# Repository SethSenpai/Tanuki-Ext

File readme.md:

# Tanuki-Ext OLED edition

The Tanuki-Ext is a redesign of the original [Tanuki Keyboard](https://github.com/SethSenpai/Tanuki). There were a few things about the original design that were preventing me from using it while coding and doing CAD. Most of all was the lack of dedicated arrow cluster. 

The Tanuki-Ext fixes these issues and aims to create and even more open and accessible keyboard platform to experiment with by moving its firmware over to [CircuitPython](https://circuitpython.org/) and [KMKfw](http://kmkfw.io/). This allows you to access and modify your code without the need for extra programs, compilers or debuggers making it very approachable.

## Layout
Like the original Tanuki keyboard the design has a split spacebar. Holding down the left spacebar brings you to the lower layer for numbers. Holding down the right spacebar brings you to the top layer for symbols. Never move your fingers from the homerow ever again!

Both the firmware and design files of the Tanuki are distributed under GNU GPLv3 and are able to be used for commercial under [specific conditions](https://choosealicense.com/licenses/gpl-3.0/).

## Assembly

Assembling the device is quite straight forward. Create the casing from the files in the `Case` folder. Grab a hold of A `PCB` or handwire the keyboard using an [Raspberry Pi Pico](https://www.raspberrypi.com/products/raspberry-pi-pico/). Put on the backplate and close the whole thing up with 4 bolts. Check out the individual folders for further instructions. 

## Keycaps
Normally a full 104 key keycap set should have enough keys to cover the keyboard properly. Just to be sure I've made a list of the needed keycaps below.

| Size | Amount |
| ---- | ------ |
| 2u | 2 |
| 1u | 37 |
| 1.25u | 8 |

I find the most comfortable keycap profile to be DSA or XDA keycaps since I don't need to worry about the keycap height being all over the place due to the uncommon layout of the Tanuki-Ext.

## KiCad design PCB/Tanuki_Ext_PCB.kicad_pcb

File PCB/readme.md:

# PCB

The PCB was designed in KiCAD 7.0. It is set up to allow you to modify it more easily. It has a couple of GPIO pins broken out as test pads. It also has footprints for WS2812 type LEDS in case you don't want to integrate an OLED screen.

## Ordering PCB
The files in the _export folder contain both the gerbers, BOM and PNP files. These files are needed for a manufacturer to know how to make your pcb. What parts to place on it, and where to place those parts.

I ordered my prototype batch through JLC pcb and the export files are formatted as such. I decided to include them to make the process of making more PCB's as smooth as possible.

If you decide to have boards made at a different manufacturer you should check their knowledge base to make sure the files you give them adhere to their guidelines.

I would not recommend soldering this PCB by hand unless you know what you're doing. Some of the parts cannot be soldered with a soldering iron and require a hot air gun.
## Library
The folder contains a library for KiCAD 7.0 that holds the footprint for the 0.9 inch OLED module that this keyboard integrates. 
## Installing the OLED
The keyboard integrates a 0.91 inch OLED Display with a resolution of 128*32. It is driven by a SSD1306. See picture below.

I bought this OLED from a local electronic parts reseller. But you can find them pretty much everywhere. Like on this [AliExpress](https://www.aliexpress.com/item/32794209149.html?spm=a2g0o.productlist.main.5.206f631a8lDb8d&algo_pvid=6620102b-a939-4291-8e9b-3f810b9d6bed&algo_exp_id=6620102b-a939-4291-8e9b-3f810b9d6bed-2&pdp_npi=3%40dis%21EUR%213.36%212.02%21%21%21%21%21%40211be3cd16882988209694634d07b1%2165792120724%21sea%21NL%21797550893&curPageLogUid=jxX5Qj7G0Q6r) listing. Just make sure the order of the pins is the same as the module shown above and that it's based on the SSD1306.

In order to install the OLED onto the PCB you need to bend its pins outward like shown in the image below.

The OLED then slots into the cutout on the board and can be soldered to the pads on the other side.

Make sure that the part where the OLED module lays on the board is covered in a piece of tape of some sort. This is to prevent potential shorts between the pads for the LEDS that are in that location and the backside of the OLED module.

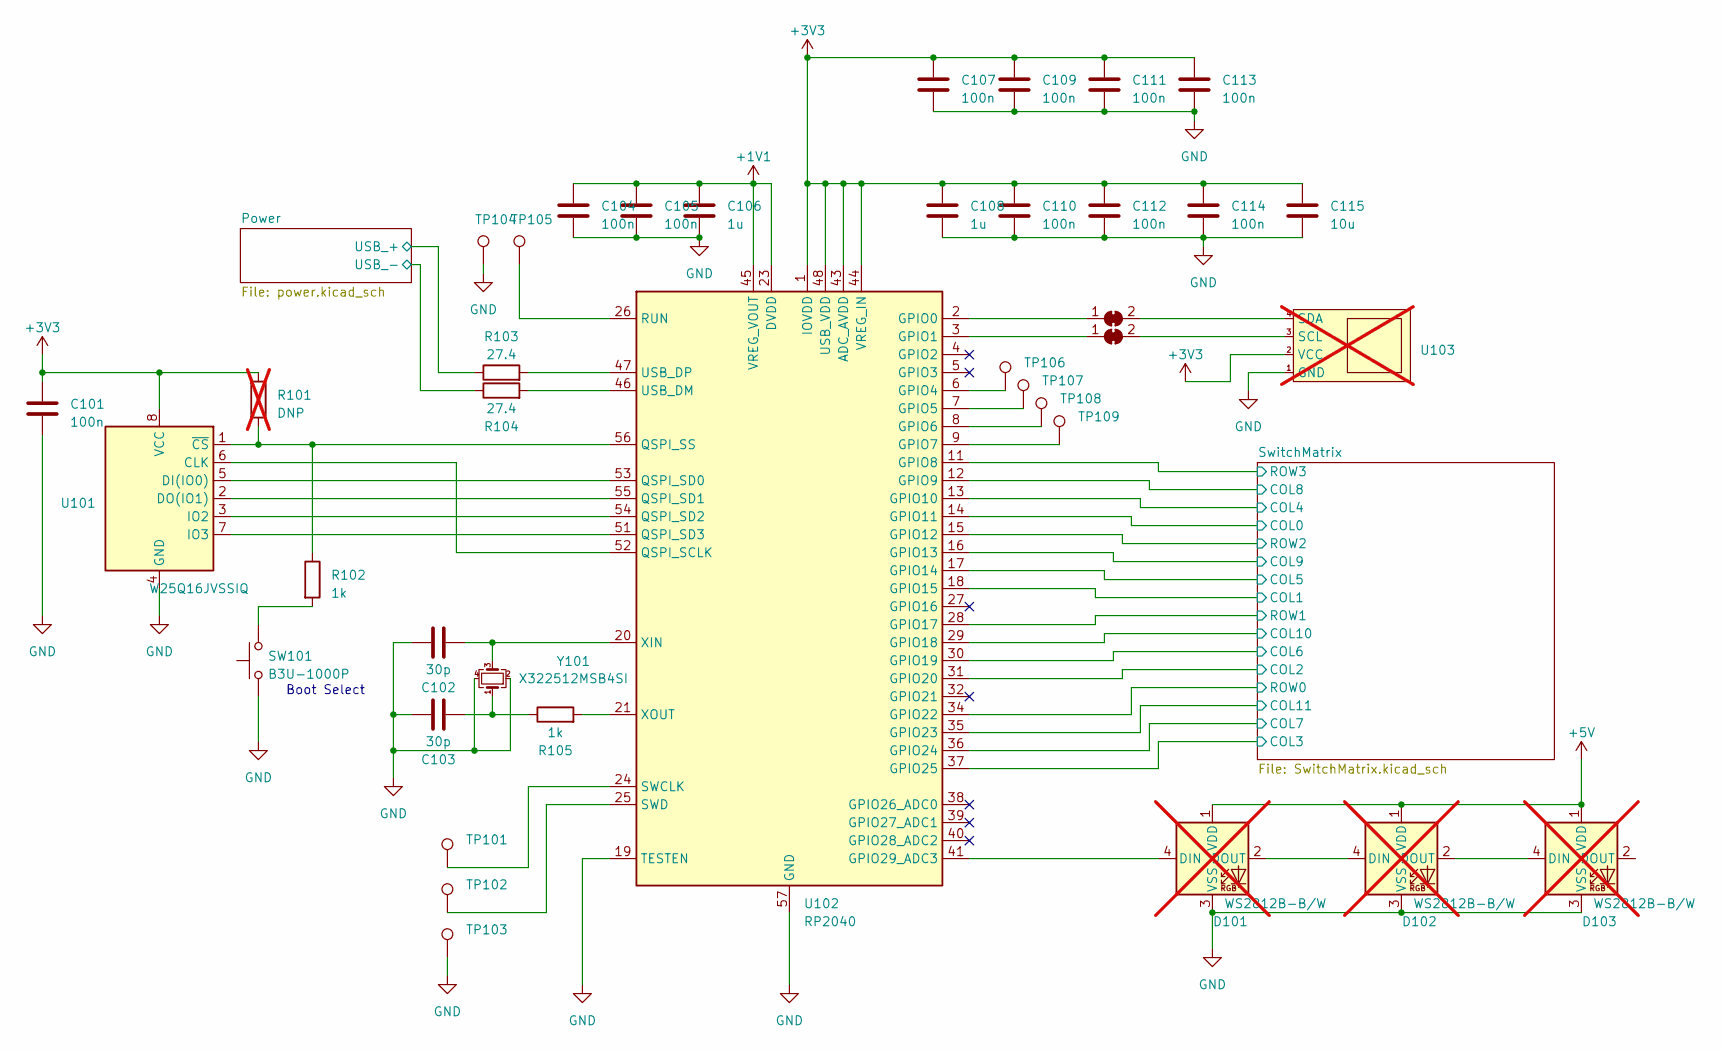
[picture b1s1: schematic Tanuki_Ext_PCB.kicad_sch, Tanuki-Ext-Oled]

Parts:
C101, C104, C105, C107, C109, C110, C111, C112, C113, C114: 100n; C_0603_1608Metric; LCSC Partnr. C14663
C102, C103: 30p; C_0603_1608Metric; LCSC Partnr. C113797
C106, C108: 1u; C_0603_1608Metric; LCSC Partnr. C14664
C115: 10u; C_0603_1608Metric; LCSC Partnr. C326057
D101, D102, D103: WS2812B-B/W; LED_WS2812B_PLCC4_5.0x5.0mm_P3.2mm; not fitted
JP101, JP102: SolderJumper_2_Bridged; SolderJumper-2_P1.3mm_Bridged_Pad1.0x1.5mm
R101: DNP; R_0603_1608Metric; not fitted
R102, R105: 1k; R_0603_1608Metric; LCSC Partnr. C22548
R103, R104: 27.4; R_0603_1608Metric; LCSC Partnr. C5126244
SW101: B3U-1000P; SW_SPST_B3U-1000P; LCSC Partnr. C231329
TP101, TP102, TP103, TP104, TP105, TP106, TP107, TP108, TP109: TestPoint; TestPoint_Pad_D1.0mm
U101: W25Q16JVSSIQ; SOIC-8_5.23x5.23mm_P1.27mm; LCSC Partnr. C82317
U102: RP2040; QFN-56-1EP_7x7mm_P0.4mm_EP3.2x3.2mm; LCSC Partnr. C2040
U103: Oled_0.91_i2c; not fitted
Y101: X322512MSB4SI; Crystal_SMD_3225-4Pin_3.2x2.5mm; LCSC Partnr. C9002

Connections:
+1V1: C104.1, C105.1, C106.1, U102.23 (DVDD), U102.45 (VREG_VOUT), U102.50 (DVDD)
/Power/USB_+: R103.1; also elsewhere on the board
/Power/USB_-: R104.1; also elsewhere on the board
/SwitchMatrix/COL0: U102.14 (GPIO11); also elsewhere on the board
/SwitchMatrix/COL1: U102.18 (GPIO15); also elsewhere on the board
/SwitchMatrix/COL2: U102.31 (GPIO20); also elsewhere on the board
/SwitchMatrix/COL3: U102.37 (GPIO25); also elsewhere on the board
/SwitchMatrix/COL4: U102.13 (GPIO10); also elsewhere on the board
/SwitchMatrix/COL5: U102.17 (GPIO14); also elsewhere on the board
/SwitchMatrix/COL6: U102.30 (GPIO19); also elsewhere on the board
/SwitchMatrix/COL7: U102.36 (GPIO24); also elsewhere on the board
/SwitchMatrix/COL8: U102.12 (GPIO9); also elsewhere on the board
/SwitchMatrix/COL9: U102.16 (GPIO13); also elsewhere on the board
/SwitchMatrix/COL10: U102.29 (GPIO18); also elsewhere on the board
/SwitchMatrix/COL11: U102.35 (GPIO23); also elsewhere on the board
/SwitchMatrix/ROW0: U102.34 (GPIO22); also elsewhere on the board
/SwitchMatrix/ROW1: U102.28 (GPIO17); also elsewhere on the board
/SwitchMatrix/ROW2: U102.15 (GPIO12); also elsewhere on the board
/SwitchMatrix/ROW3: U102.11 (GPIO8); also elsewhere on the board
GND: C101.2, C102.2, C103.2, C104.2, C105.2, C106.2, C107.2, C108.2, C109.2, C110.2, C111.2, C112.2, C113.2, C114.2, C115.2, D101.3 (VSS), D102.3 (VSS), D103.3 (VSS), SW101.1, TP103.1, TP104.1, U101.4 (GND), U102.19 (TESTEN), U102.57 (GND), U103.1 (GND), Y101.2, Y101.4; also elsewhere on the board
unnamed: C103.1, R105.1, Y101.1
unnamed: D101.4 (DIN), U102.41 (GPIO29_ADC3)
unnamed: D101.2 (DOUT), D102.4 (DIN)
unnamed: D102.2 (DOUT), D103.4 (DIN)
unnamed: JP101.1 (A), U102.2 (GPIO0)
unnamed: JP101.2 (B), U103.4 (SDA)
unnamed: JP102.1 (A), U102.3 (GPIO1)
unnamed: JP102.2 (B), U103.3 (SCL)
unnamed: R102.2, SW101.2
unnamed: U101.6 (CLK), U102.52 (QSPI_SCLK)
unnamed: U101.5 (DI(IO0)), U102.53 (QSPI_SD0)
unnamed: U101.2 (DO(IO1)), U102.55 (QSPI_SD1)
unnamed: U101.3 (IO2), U102.54 (QSPI_SD2)
unnamed: U101.7 (IO3), U102.51 (QSPI_SD3)
unnamed: R101.2, R102.1, U101.1 (~CS), U102.56 (QSPI_SS)
unnamed: TP106.1, U102.6 (GPIO4)
unnamed: TP107.1, U102.7 (GPIO5)
unnamed: TP108.1, U102.8 (GPIO6)
unnamed: TP105.1, U102.26 (RUN)
unnamed: TP101.1, U102.24 (SWCLK)
unnamed: TP102.1, U102.25 (SWD)
unnamed: R104.2, U102.46 (USB_DM)
unnamed: R103.2, U102.47 (USB_DP)
unnamed: C102.1, U102.20 (XIN), Y101.3
unnamed: R105.2, U102.21 (XOUT)

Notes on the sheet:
Boot Select

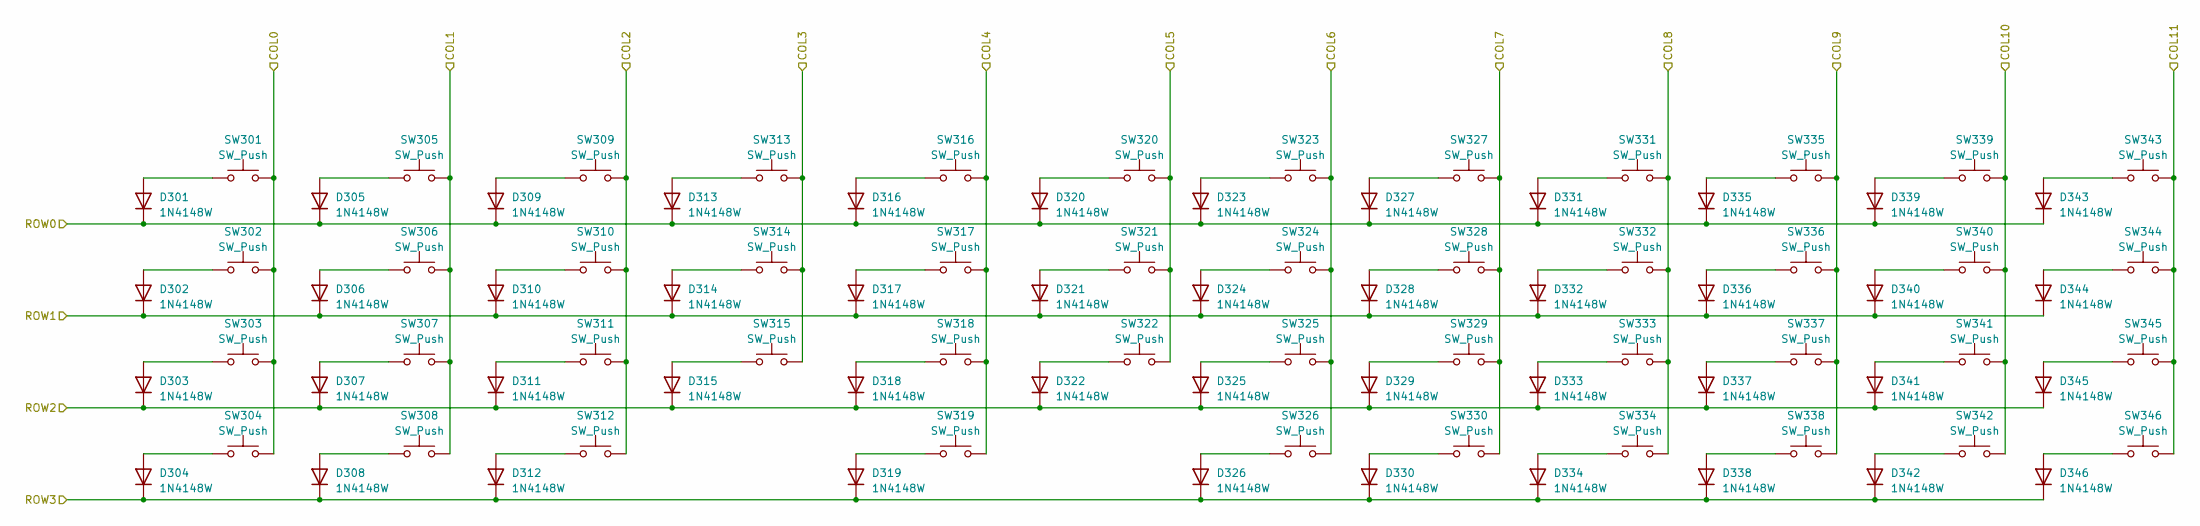
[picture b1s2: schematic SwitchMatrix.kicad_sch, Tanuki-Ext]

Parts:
D301, D302, D303, D304, D305, D306, D307, D308, D309, D310, D311, D312, D313, D314, D315, D316, D317, D318, D319, D320, D321, D322, D323, D324, D325, D326, D327, D328, D329, D330, D331, D332, D333, D334, D335, D336, D337, D338, D339, D340, D341, D342, D343, D344, D345, D346: 1N4148W; D_SOD-123F; LCSC Partnr. C444720
SW301, SW302, SW303, SW304, SW308, SW334, SW343, SW344: SW_Push; SW_Cherry_MX_PCB_1.25u
SW305, SW306, SW307, SW309, SW310, SW311, SW312, SW313, SW314, SW315, SW316, SW317, SW318, SW320, SW321, SW322, SW323, SW324, SW325, SW327, SW328, SW329, SW330, SW331, SW332, SW333, SW335, SW336, SW337, SW338, SW339, SW340, SW341, SW342, SW345, SW346: SW_Push; SW_Cherry_MX_PCB_1.00u
SW319, SW326: SW_Push; SW_Cherry_MX_PCB_2.00u

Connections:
/SwitchMatrix/COL0: SW301.2, SW302.2, SW303.2, SW304.2; also elsewhere on the board
/SwitchMatrix/COL1: SW305.2, SW306.2, SW307.2, SW308.2; also elsewhere on the board
/SwitchMatrix/COL2: SW309.2, SW310.2, SW311.2, SW312.2; also elsewhere on the board
/SwitchMatrix/COL3: SW313.2, SW314.2, SW315.2; also elsewhere on the board
/SwitchMatrix/COL4: SW316.2, SW317.2, SW318.2, SW319.2; also elsewhere on the board
/SwitchMatrix/COL5: SW320.2, SW321.2, SW322.2; also elsewhere on the board
/SwitchMatrix/COL6: SW323.2, SW324.2, SW325.2, SW326.2; also elsewhere on the board
/SwitchMatrix/COL7: SW327.2, SW328.2, SW329.2, SW330.2; also elsewhere on the board
/SwitchMatrix/COL8: SW331.2, SW332.2, SW333.2, SW334.2; also elsewhere on the board
/SwitchMatrix/COL9: SW335.2, SW336.2, SW337.2, SW338.2; also elsewhere on the board
/SwitchMatrix/COL10: SW339.2, SW340.2, SW341.2, SW342.2; also elsewhere on the board
/SwitchMatrix/COL11: SW343.2, SW344.2, SW345.2, SW346.2; also elsewhere on the board
/SwitchMatrix/ROW0: D301.1 (K), D305.1 (K), D309.1 (K), D313.1 (K), D316.1 (K), D320.1 (K), D323.1 (K), D327.1 (K), D331.1 (K), D335.1 (K), D339.1 (K), D343.1 (K); also elsewhere on the board
/SwitchMatrix/ROW1: D302.1 (K), D306.1 (K), D310.1 (K), D314.1 (K), D317.1 (K), D321.1 (K), D324.1 (K), D328.1 (K), D332.1 (K), D336.1 (K), D340.1 (K), D344.1 (K); also elsewhere on the board
/SwitchMatrix/ROW2: D303.1 (K), D307.1 (K), D311.1 (K), D315.1 (K), D318.1 (K), D322.1 (K), D325.1 (K), D329.1 (K), D333.1 (K), D337.1 (K), D341.1 (K), D345.1 (K); also elsewhere on the board
/SwitchMatrix/ROW3: D304.1 (K), D308.1 (K), D312.1 (K), D319.1 (K), D326.1 (K), D330.1 (K), D334.1 (K), D338.1 (K), D342.1 (K), D346.1 (K); also elsewhere on the board
unnamed: D301.2 (A), SW301.1
unnamed: D302.2 (A), SW302.1
unnamed: D303.2 (A), SW303.1
unnamed: D304.2 (A), SW304.1
unnamed: D305.2 (A), SW305.1
unnamed: D306.2 (A), SW306.1
unnamed: D307.2 (A), SW307.1
unnamed: D308.2 (A), SW308.1
unnamed: D309.2 (A), SW309.1
unnamed: D310.2 (A), SW310.1
unnamed: D311.2 (A), SW311.1
unnamed: D312.2 (A), SW312.1
unnamed: D313.2 (A), SW313.1
unnamed: D314.2 (A), SW314.1
unnamed: D315.2 (A), SW315.1
unnamed: D316.2 (A), SW316.1
unnamed: D317.2 (A), SW317.1
unnamed: D318.2 (A), SW318.1
unnamed: D319.2 (A), SW319.1
unnamed: D320.2 (A), SW320.1
unnamed: D321.2 (A), SW321.1
unnamed: D322.2 (A), SW322.1
unnamed: D323.2 (A), SW323.1
unnamed: D324.2 (A), SW324.1
unnamed: D325.2 (A), SW325.1
unnamed: D326.2 (A), SW326.1
unnamed: D327.2 (A), SW327.1
unnamed: D328.2 (A), SW328.1
unnamed: D329.2 (A), SW329.1
unnamed: D330.2 (A), SW330.1
unnamed: D331.2 (A), SW331.1
unnamed: D332.2 (A), SW332.1
unnamed: D333.2 (A), SW333.1
unnamed: D334.2 (A), SW334.1
unnamed: D335.2 (A), SW335.1
unnamed: D336.2 (A), SW336.1
unnamed: D337.2 (A), SW337.1
unnamed: D338.2 (A), SW338.1
unnamed: D339.2 (A), SW339.1
unnamed: D340.2 (A), SW340.1
unnamed: D341.2 (A), SW341.1
unnamed: D342.2 (A), SW342.1
unnamed: D343.2 (A), SW343.1
unnamed: D344.2 (A), SW344.1
unnamed: D345.2 (A), SW345.1
unnamed: D346.2 (A), SW346.1

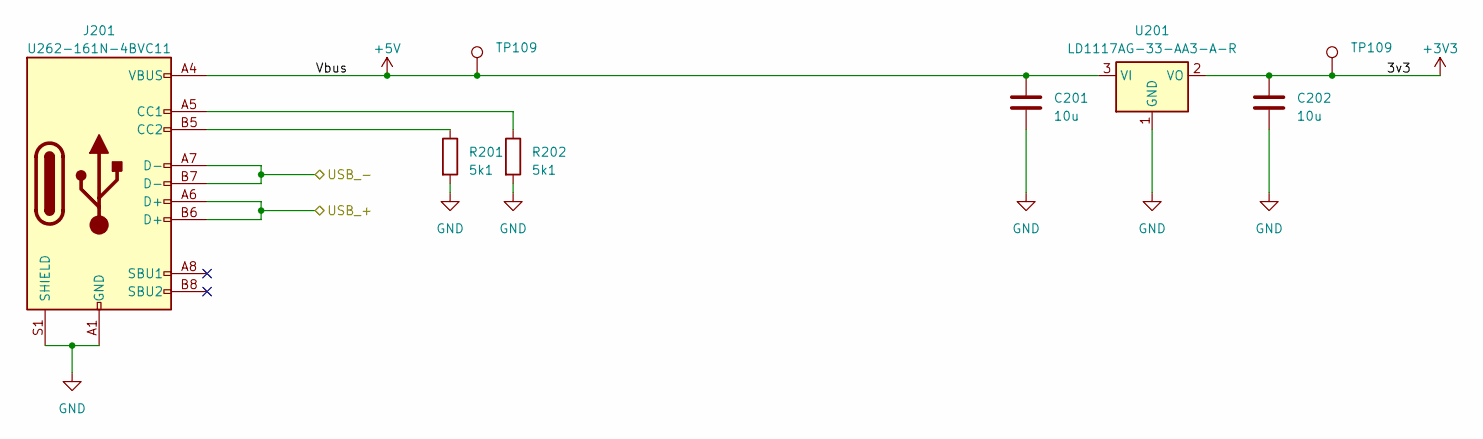
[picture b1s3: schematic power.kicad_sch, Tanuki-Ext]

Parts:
C201, C202: 10u; C_0603_1608Metric; LCSC Partnr. C326057
J201: U262-161N-4BVC11; USB_C_Receptacle_XKB_U262-16XN-4BVC11; LCSC Partnr. C319148
R201, R202: 5k1; R_0603_1608Metric; LCSC Partnr. C105580
TP109: TestPoint; TestPoint_Pad_D1.0mm
U201: LD1117AG-33-AA3-A-R; SOT-223-3_TabPin2; LCSC Partnr. C71121

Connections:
/Power/USB_+: J201.A6 (D+), J201.B6 (D+); also elsewhere on the board
/Power/USB_-: J201.A7 (D-), J201.B7 (D-); also elsewhere on the board
GND: C201.2, C202.2, J201.A1 (GND), J201.A12 (GND), J201.B1 (GND), J201.B12 (GND), J201.S1 (SHIELD), R201.2, R202.2, U201.1 (GND); also elsewhere on the board
unnamed: J201.A5 (CC1), R202.1
unnamed: J201.B5 (CC2), R201.1

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
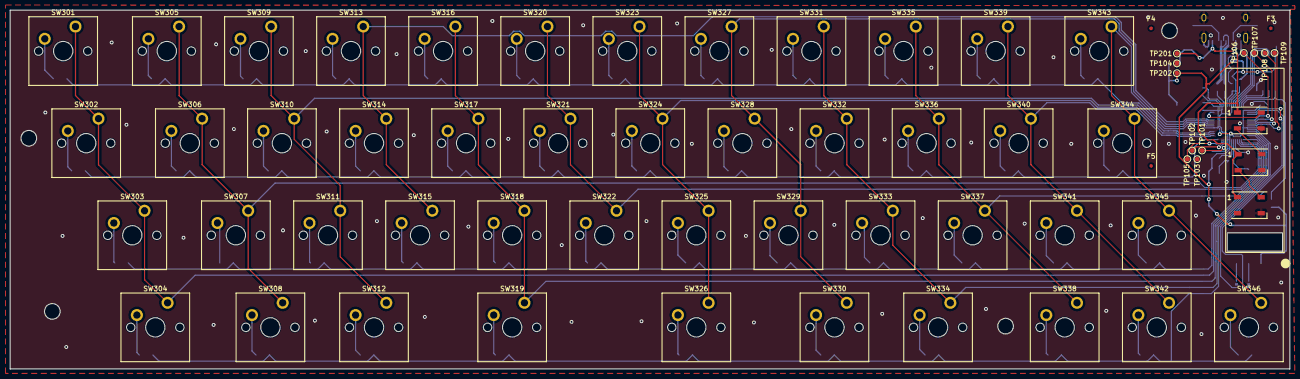
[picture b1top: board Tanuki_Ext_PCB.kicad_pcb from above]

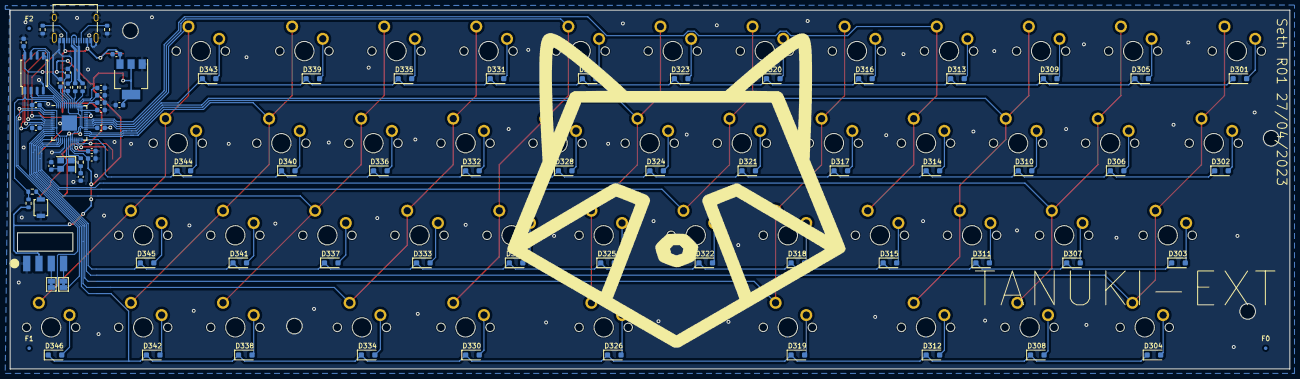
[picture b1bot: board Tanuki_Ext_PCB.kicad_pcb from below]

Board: 2 copper layers, 264.7 x 74.2 mm, 145 parts (81 on the bottom side), 96 nets.

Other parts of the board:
F0, F1, F2, F3, F4, F5: Fiducial_0.75mm_Mask1.5mm
TP201, TP202: TestPoint; TestPoint_Pad_D1.0mm

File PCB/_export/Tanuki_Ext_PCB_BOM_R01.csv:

Comment,Designator,Footprint,LCSC
100n,"C101,C104,C105,C107,C109,C110,C111,C112,C113,C114",Capacitor_SMD:C_0603_1608Metric,C14663
30p,"C102,C103",Capacitor_SMD:C_0603_1608Metric,C113797
1u,"C106,C108",Capacitor_SMD:C_0603_1608Metric,C14664
10u,"C115,C201,C202",Capacitor_SMD:C_0603_1608Metric,C326057
1N4148W,"D301,D302,D303,D304,D305,D306,D307,D308,D309,D310,D311,D312,D313,D314,D315,D316,D317,D318,D319,D320,D321,D322,D323,D324,D325,D326,D327,D328,D329,D330,D331,D332,D333,D334,D335,D336,D337,D338,D339,D340,D341,D342,D343,D344,D345,D346",Diode_SMD:D_SOD-123F,C444720
U262-161N-4BVC11,J201,Connector_USB:USB_C_Receptacle_XKB_U262-16XN-4BVC11,C319148
1k,"R102,R105",Resistor_SMD:R_0603_1608Metric,C22548
27.4,"R103,R104",Resistor_SMD:R_0603_1608Metric,C5126244
5k1,"R201,R202",Resistor_SMD:R_0603_1608Metric,C105580
B3U-1000P,SW101,Button_Switch_SMD:SW_SPST_B3U-1000P,C231329
W25Q16JVSSIQ,U101,Package_SO:SOIC-8_5.23x5.23mm_P1.27mm,C82317
RP2040,U102,Package_DFN_QFN:QFN-56-1EP_7x7mm_P0.4mm_EP3.2x3.2mm,C2040
LD1117AG-33-AA3-A-R ,U201,Package_TO_SOT_SMD:SOT-223-3_TabPin2,C71121
X322512MSB4SI,Y101,Crystal:Crystal_SMD_3225-4Pin_3.2x2.5mm,C9002

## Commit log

2023-05-30 inital commit
2023-05-30 removed some extranious files
2023-07-01 added readme for case
2023-07-01 readme for case
2023-07-02 added readme's
